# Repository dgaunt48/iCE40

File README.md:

# iCE40
Various iCE40 FPGA Projects.

## DaveFPGA
My custom iCE40 FPGA boards, see readme there for full description.

## iCE1k_VGA111
Display a 3bit VGA RGB test pattern on my iCE40hx1k based board.

## VIA_6522
6522 VIA iCE40 FPGA Core is now running on a real Vic20 and passing all tests on the diagnostic cartridge. It will boot to BASIC with the FPGA running the timers, performing the keyboard matrix scan and reading / writing serial data to the 1541.

## VIC_6560
Initial tests to recreate the VIC 6560 video IC.

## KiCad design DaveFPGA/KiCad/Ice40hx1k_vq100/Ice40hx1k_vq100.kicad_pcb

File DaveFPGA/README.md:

# Source
Skeleton rp2354 project to create a 25mhz clock and upload the FPGA bitstream.

# KiCAD\iCE40hx1k
My custom iCE40hx1k FPGA board with rp2354a I use when prototyping.

## Features
- Direct programming via SWD from the pico.
- Auto reset and much faster turn-around time than my other FT232H board.
- Cheaper BOM as both spi flash IC's are no longer needed.
- 3 Bit VGA from the pico for debugging.
- 2 User defined clock frequencies available from the pico.
- Upto 19 3v3 IO pins available to / from the pico.
- 40 5v <-> 3v3 bi-directional level shifters avaliable (some shared to the pico).
- 24 5v <-> 3v3 bi-directional open drain level shifters.
- Second 3 Bit VGA connector is availble from the FPGA.
- [link to ibom](KiCad/ibom_iCE40hx1k_vq100.html)

# KiCAD\iCE40hx4k
FT232H based iCE40hx4k board.  Not using this much anymore as i like
the workflow from the pico SWD.  Will probably make a new version of
this more like the 1k board when I need more IO pins or bitstream space.

## Features
- SPI flash programmed directly via FT232H.
- No direct control via the pico.
- Pico can be left running and reload the FPGA bitstream.
- [link to ibom](KiCad/ibom_iCE40hx4k_tq144.html)

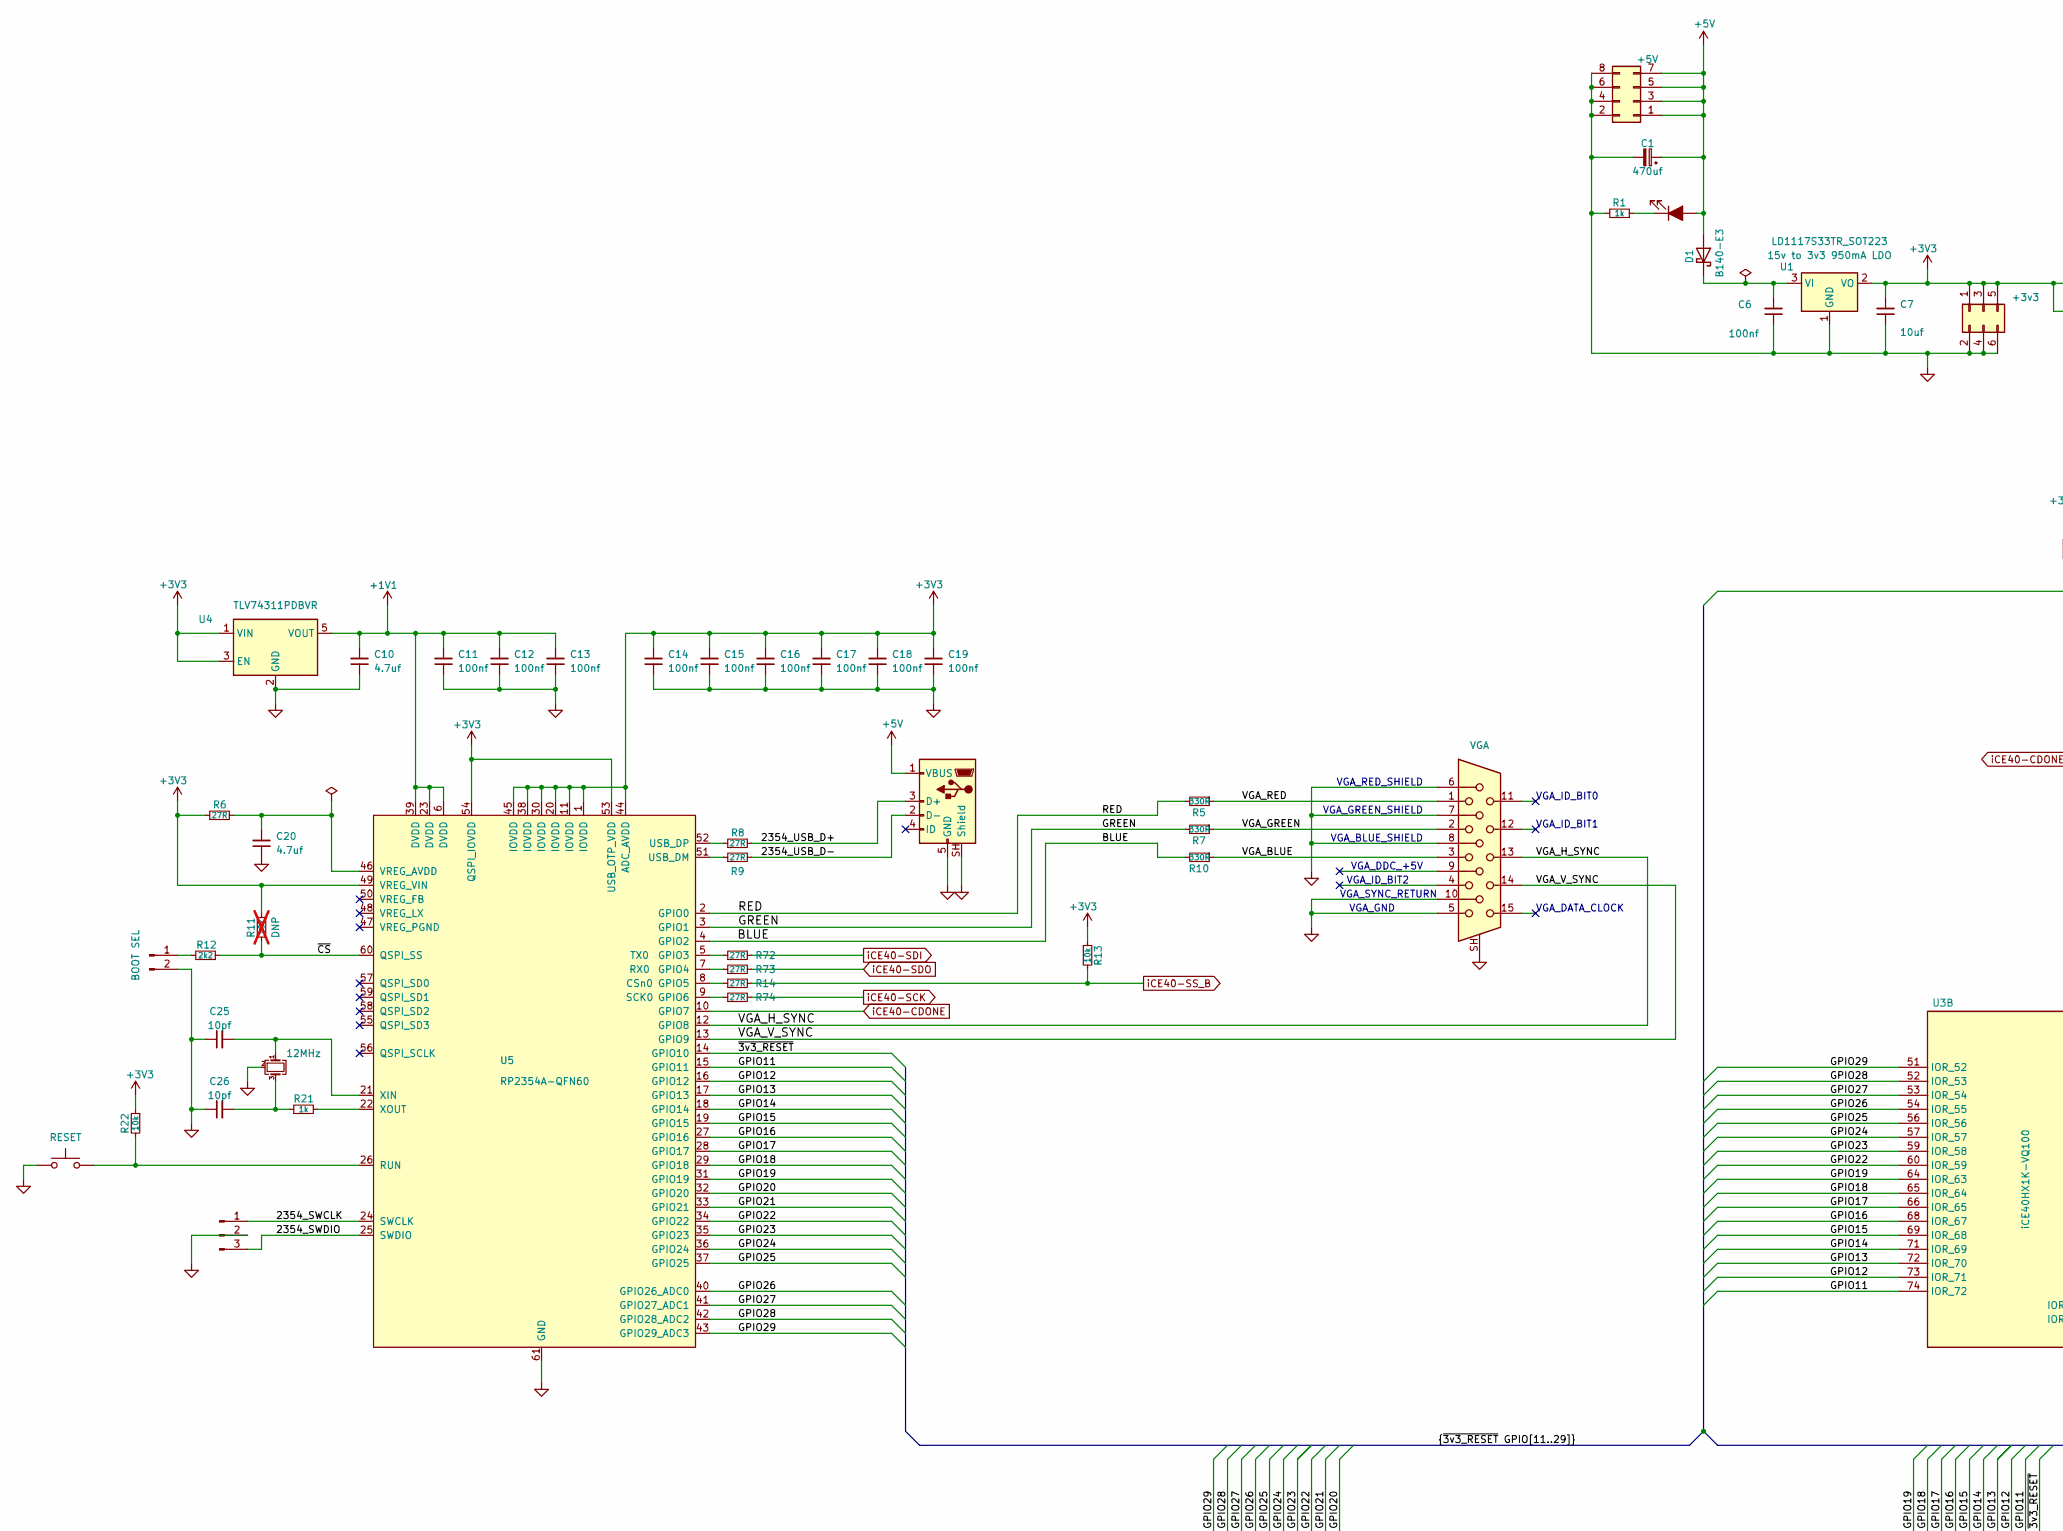
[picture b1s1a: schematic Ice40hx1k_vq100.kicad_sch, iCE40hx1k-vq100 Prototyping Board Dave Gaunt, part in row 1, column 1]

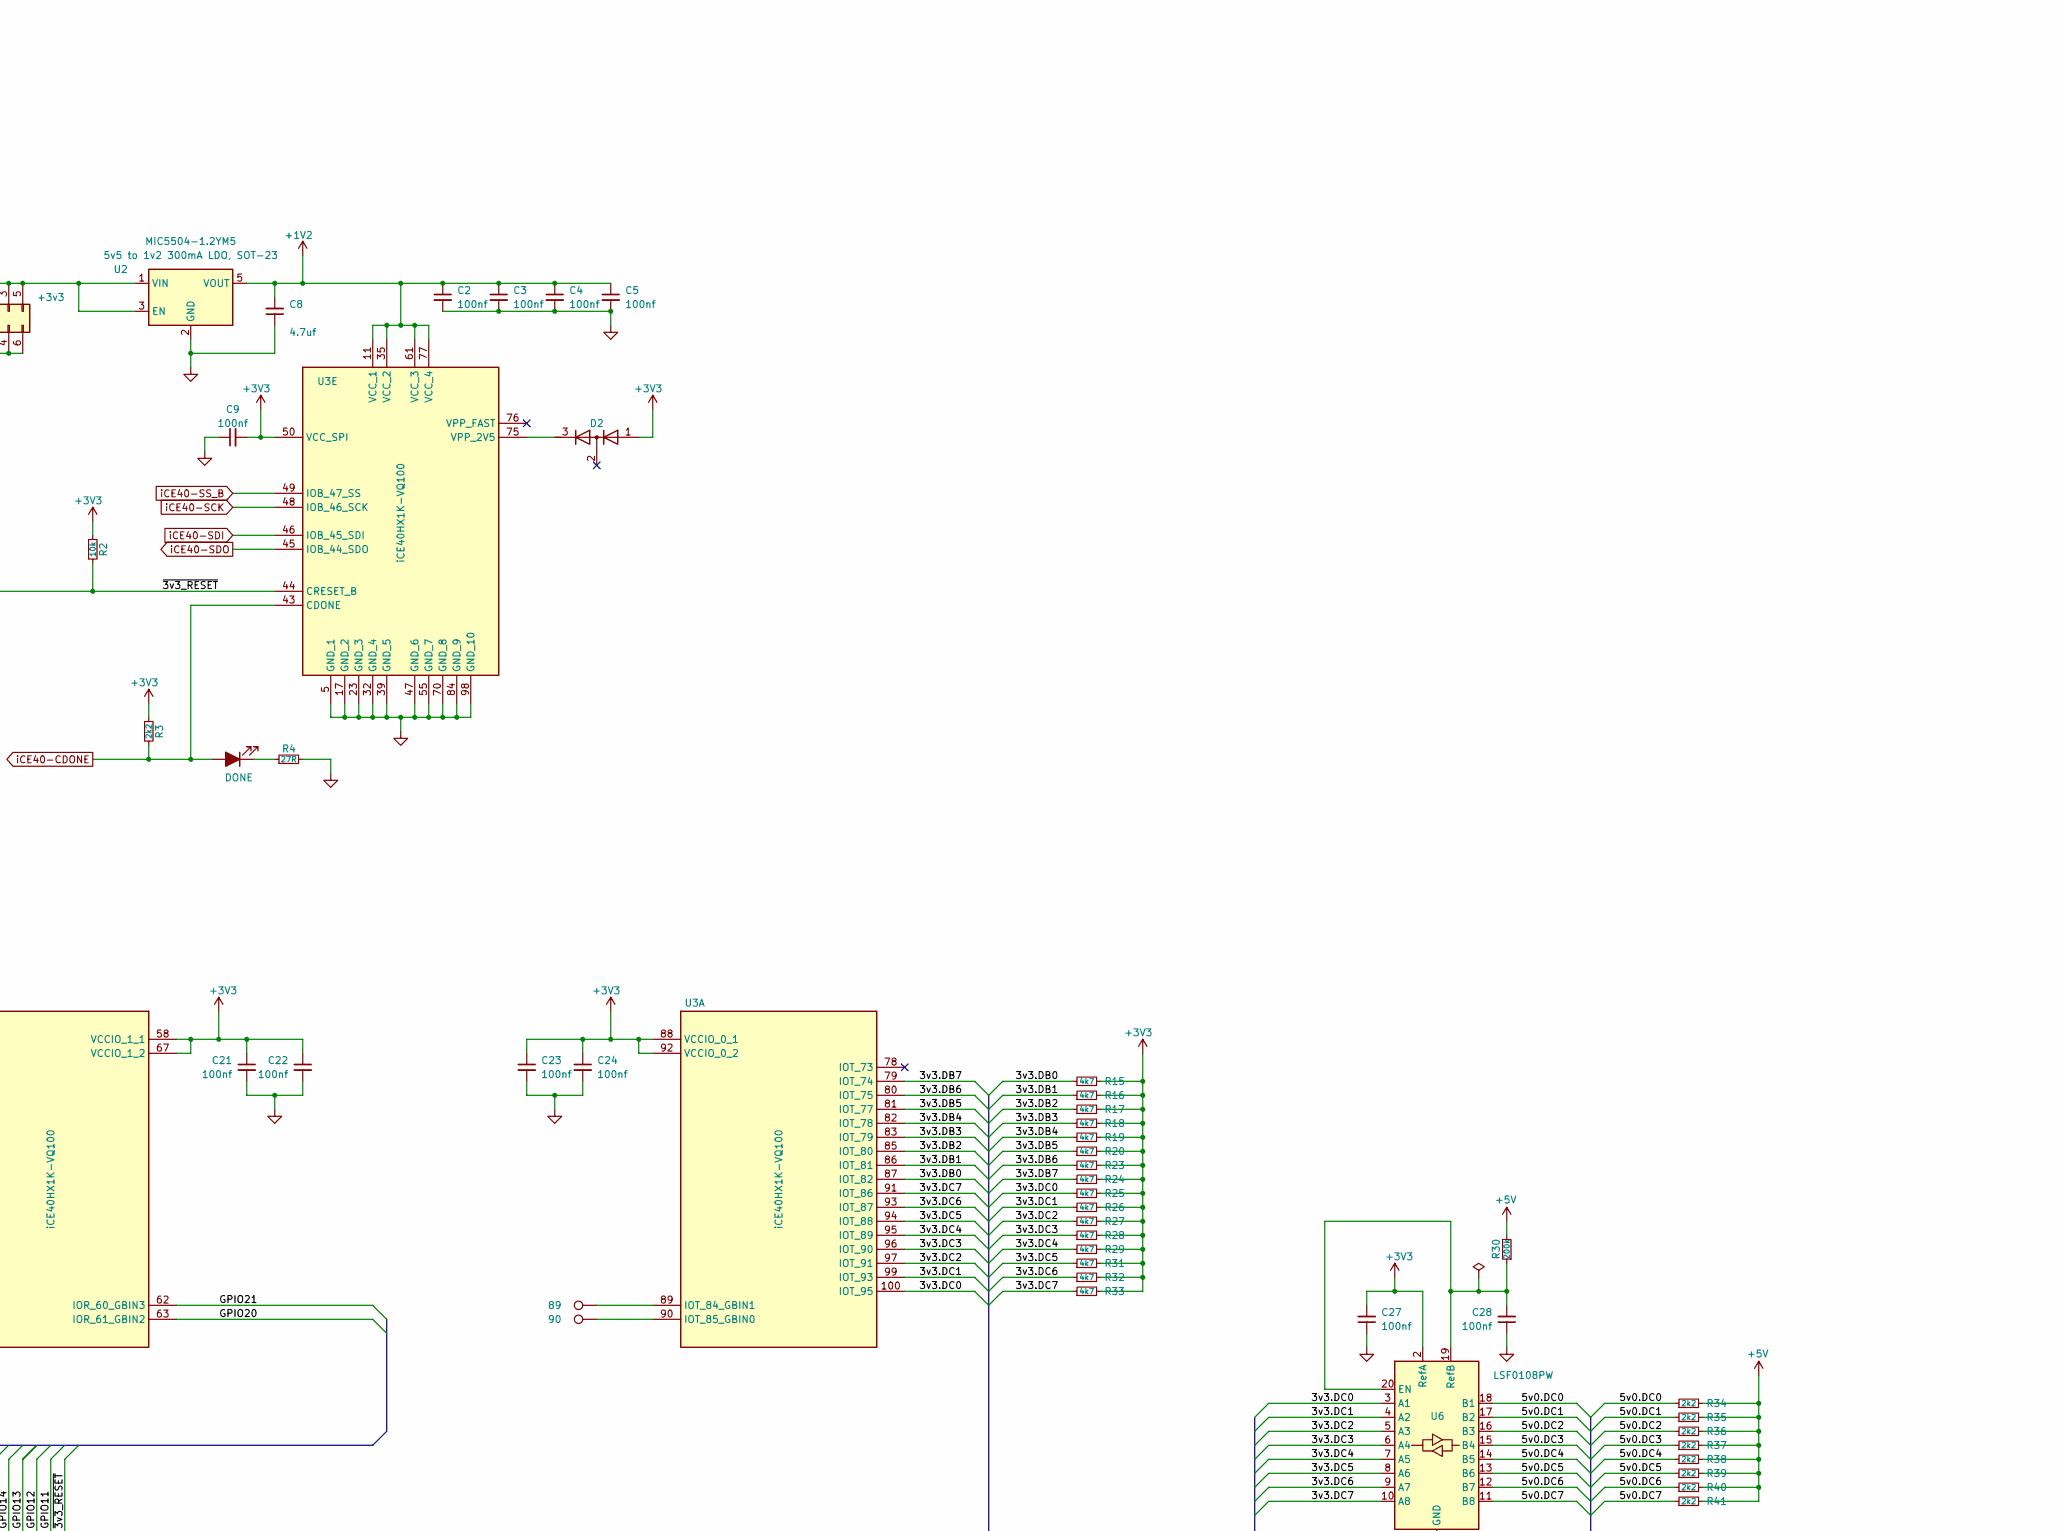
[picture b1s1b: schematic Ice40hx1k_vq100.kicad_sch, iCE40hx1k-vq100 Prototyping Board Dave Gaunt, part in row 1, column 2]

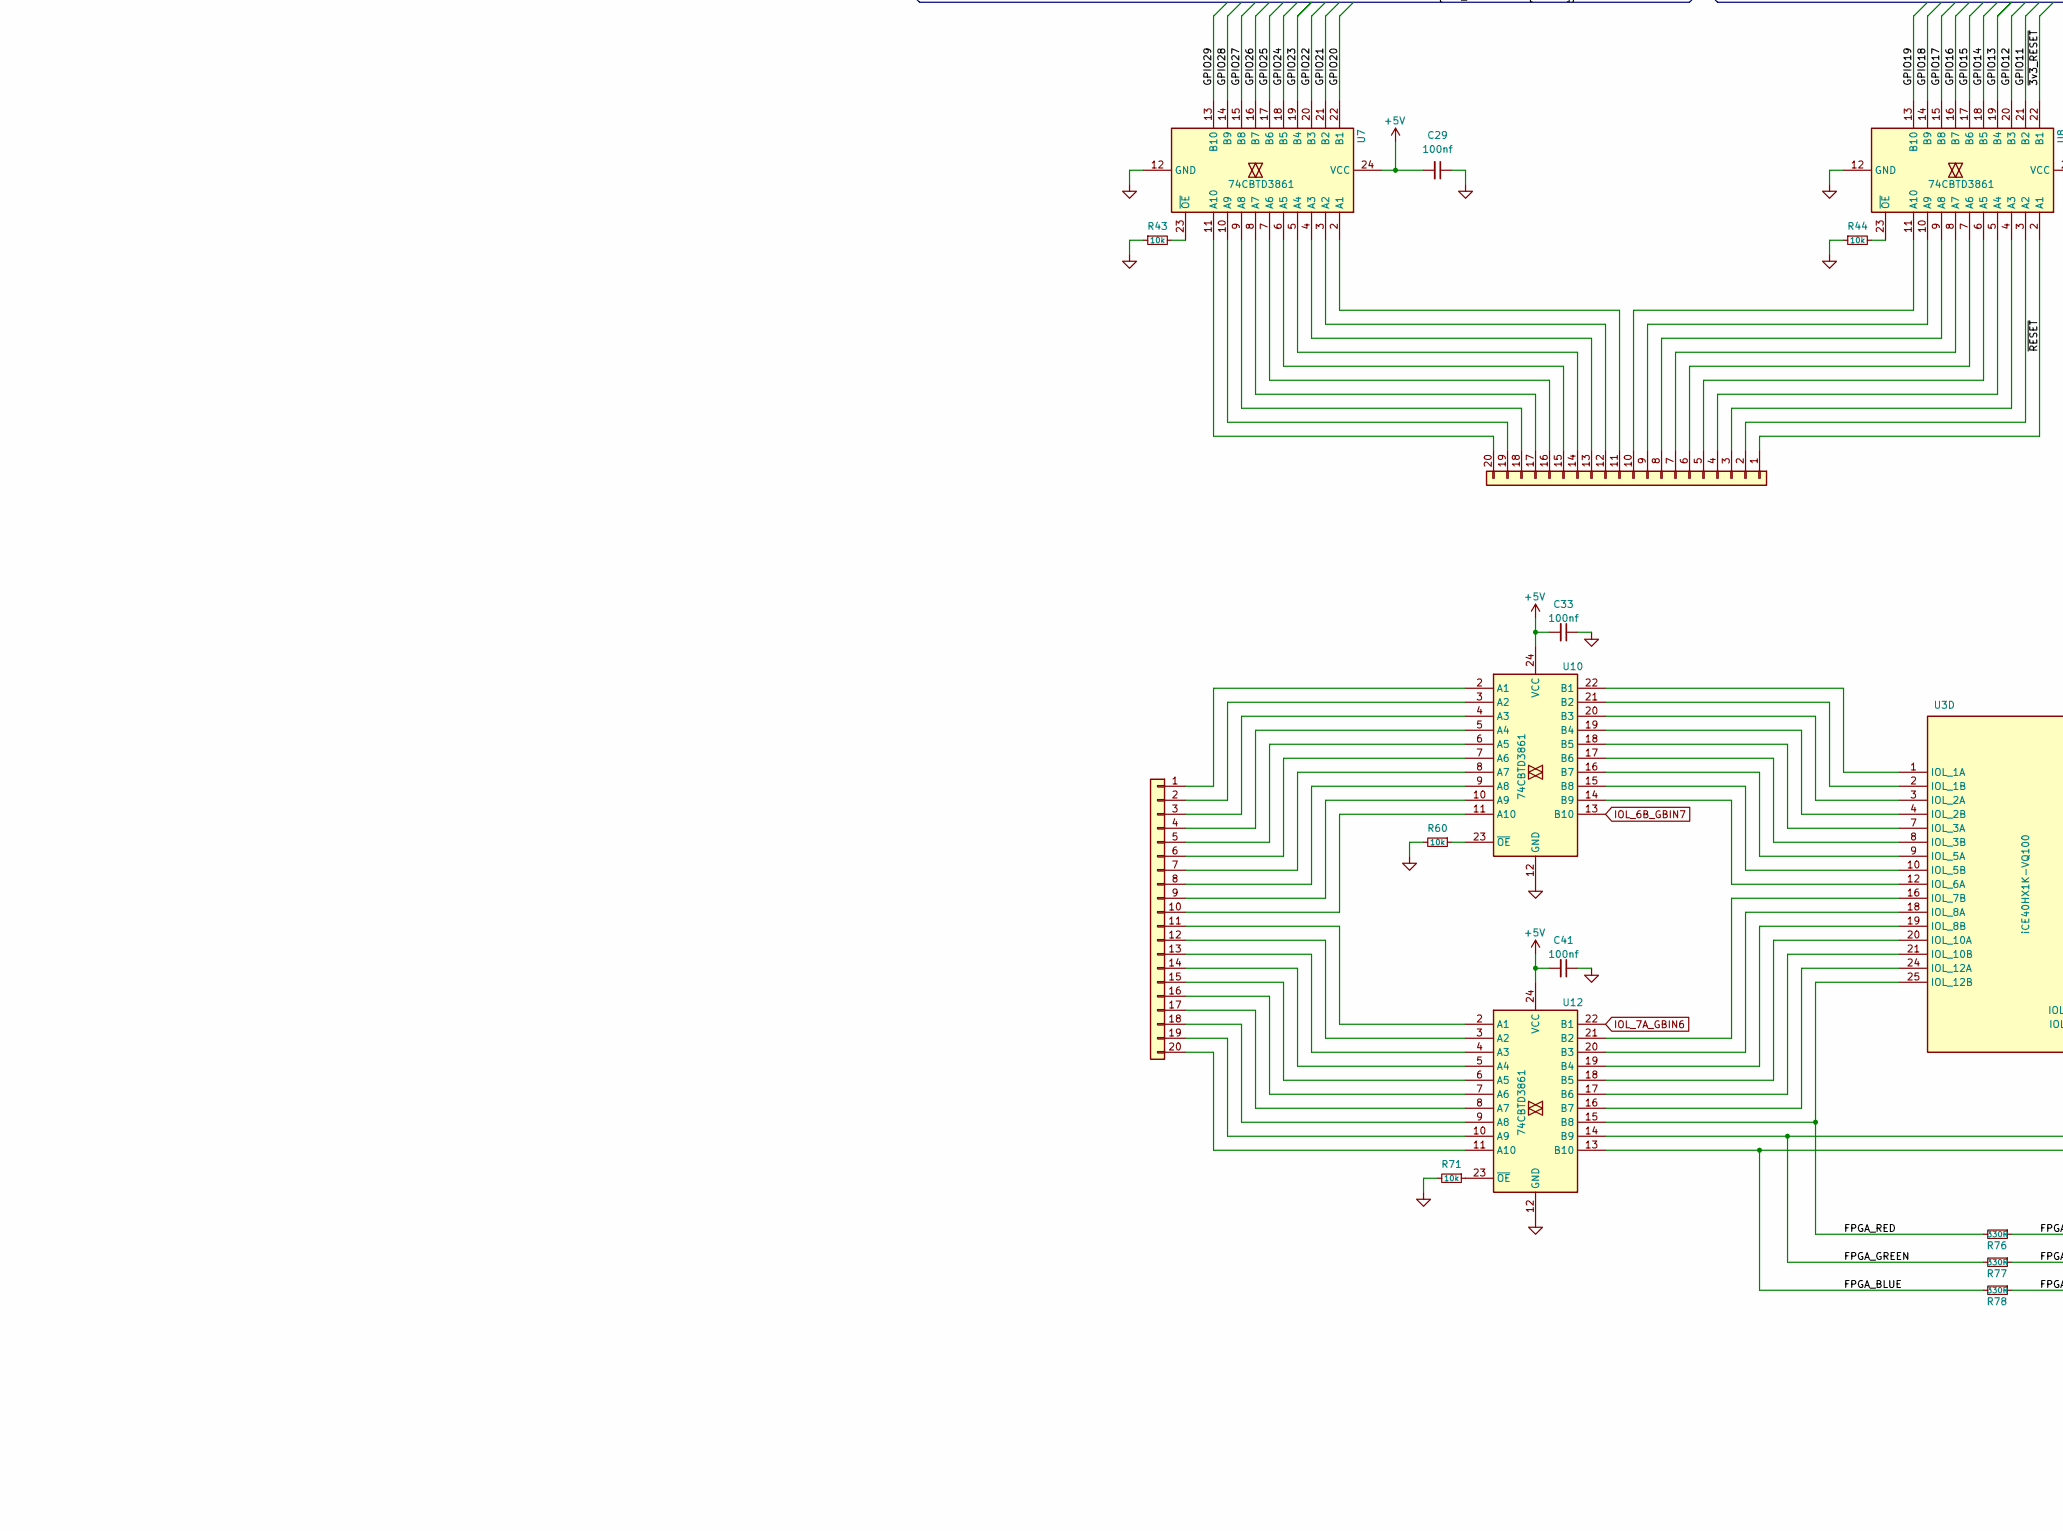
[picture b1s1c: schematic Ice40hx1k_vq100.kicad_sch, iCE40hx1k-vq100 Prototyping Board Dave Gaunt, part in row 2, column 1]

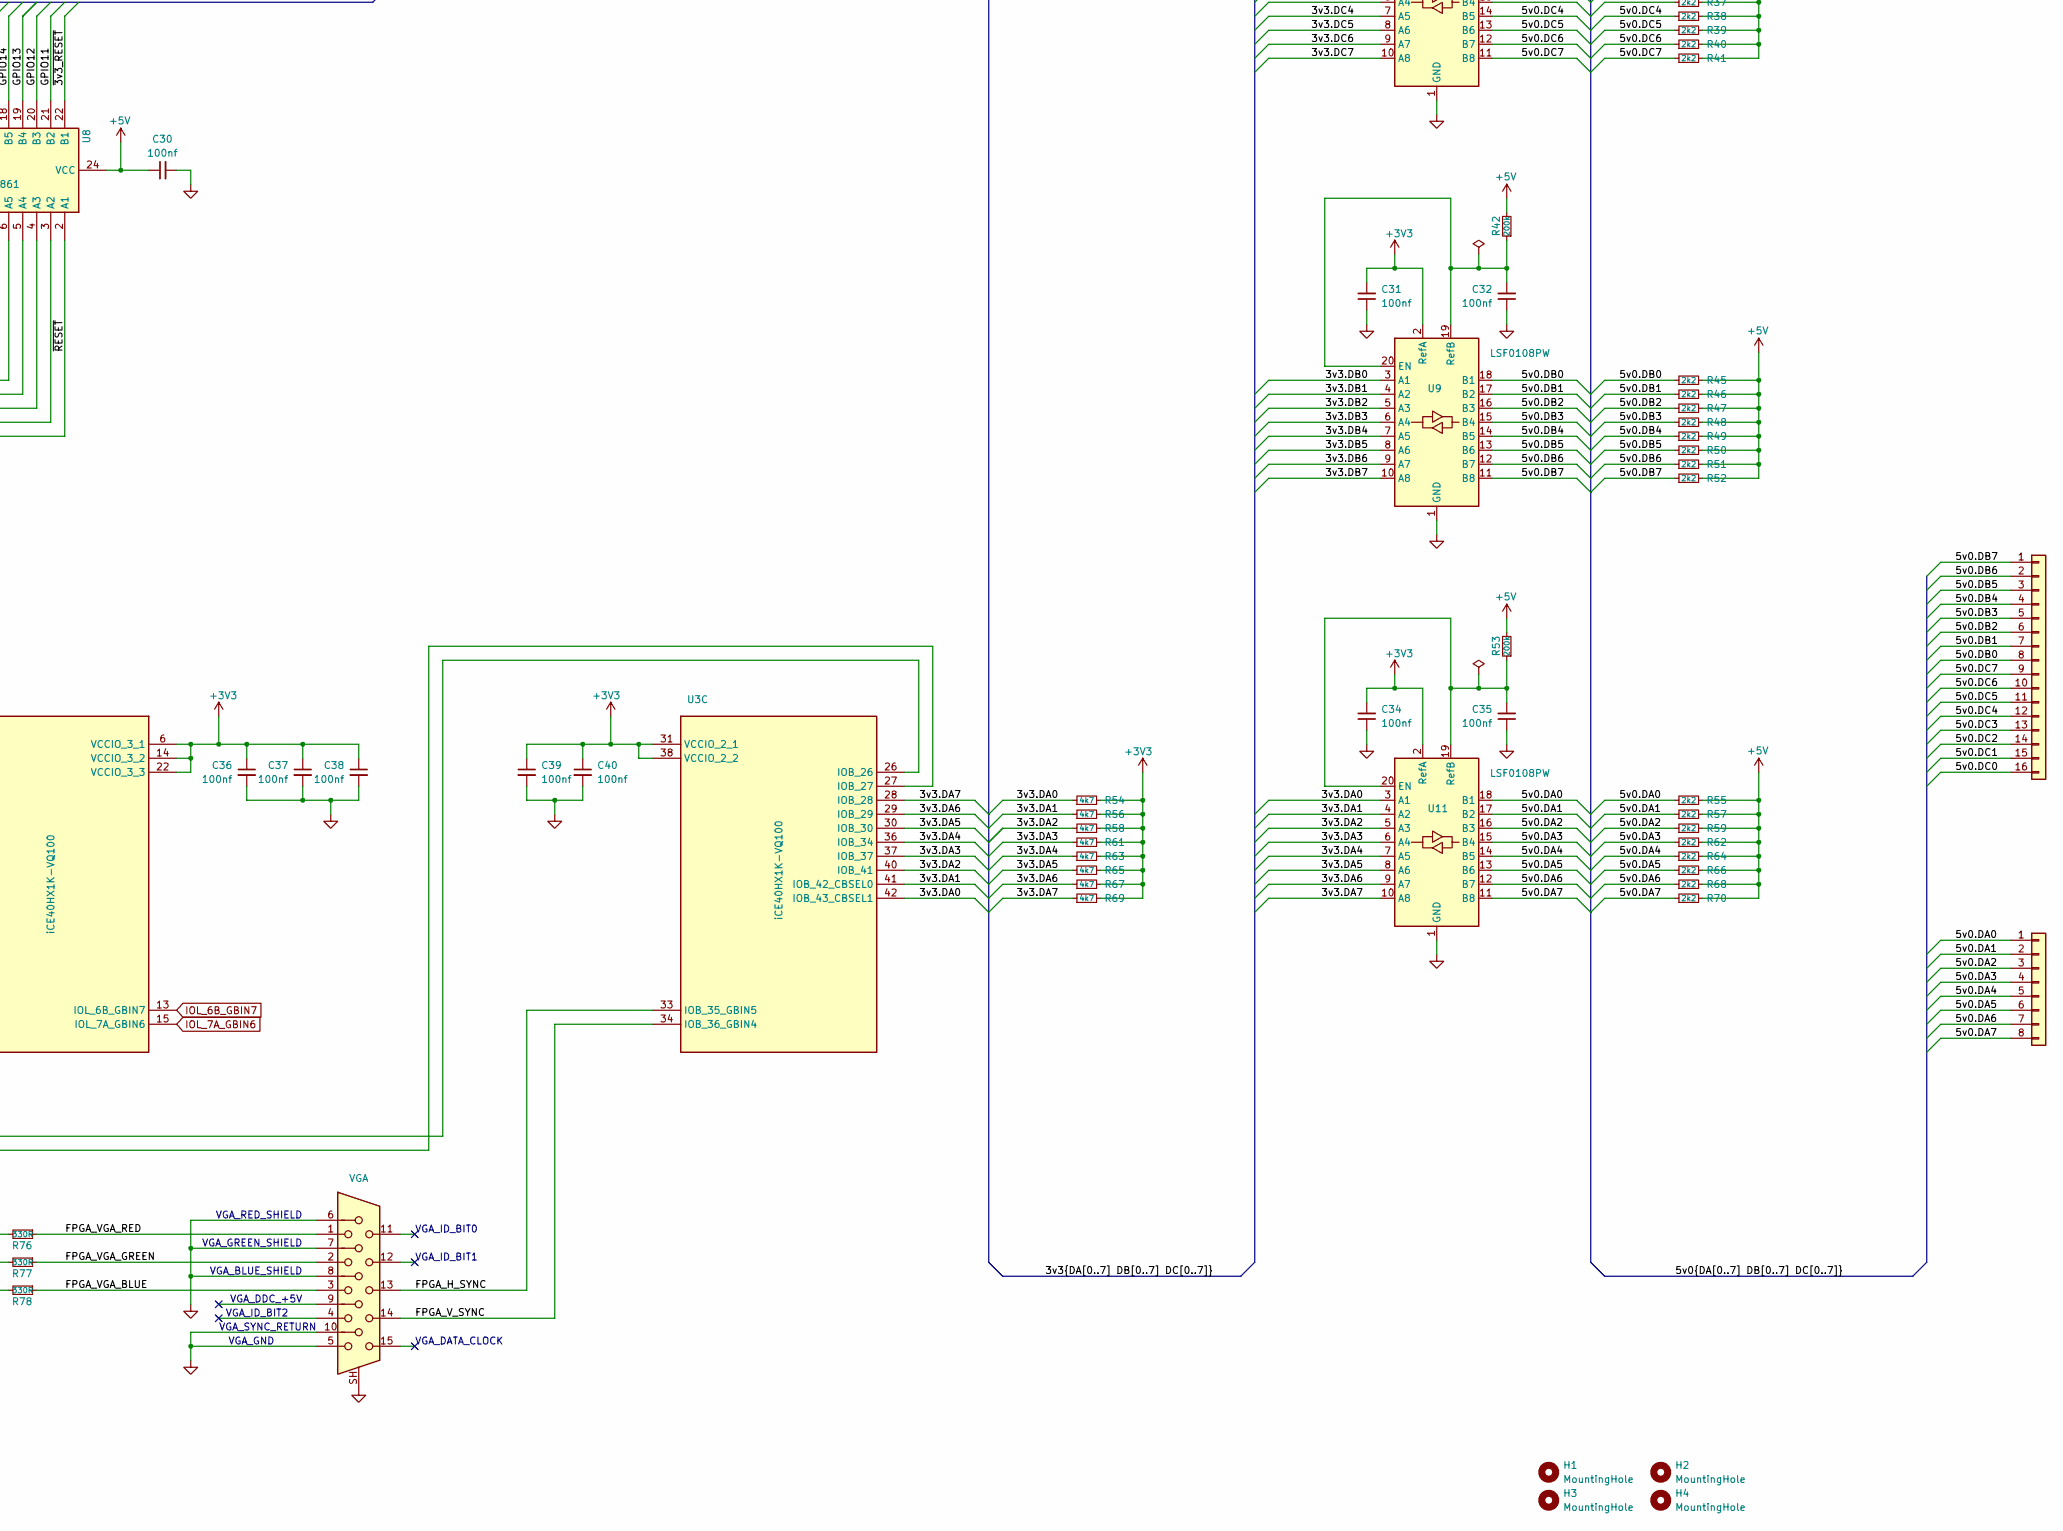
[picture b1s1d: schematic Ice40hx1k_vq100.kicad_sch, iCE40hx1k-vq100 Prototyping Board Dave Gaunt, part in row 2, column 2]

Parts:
C1: 470uf; CP_Radial_D5.0mm_P2.50mm
C2, C3, C4, C5, C6, C9, C11, C12, C13, C14, C15, C16, C17, C18, C19, C21, C22, C23, C24, C27, C28, C29, C30, C31, C32, C33, C34, C35, C36, C37, C38, C39, C40, C41: 100nf; C_0603_1608Metric
C7: 10uf; C_0805_2012Metric
C8, C10, C20: 4.7uf; C_0603_1608Metric
C25, C26: 10pf; C_0603_1608Metric
CDone1: DONE; LED_0805_2012Metric
D1: B140-E3; D_SOD-123
D2: D_Dual_Series_ACK; SOT-23
H1, H2, H3, H4: MountingHole; MountingHole_3.5mm
J1: +5V; PinHeader_2x04_P2.54mm_Vertical
J2: +3v3; PinHeader_2x03_P2.54mm_Vertical
J3: USB_B_Micro; USB_Micro-B_Amphenol_10103594-0001LF_Horizontal
J4, J10: VGA; DSUB-15
J5: SWD; PinHeader_1x03_P2.54mm_Vertical
J6, J8: PinHeader_1x20_P2.54mm_Vertical
J7: PinHeader_1x16_P2.54mm_Vertical
J9: PinHeader_1x08_P2.54mm_Vertical
Je1: BOOT SEL; PinHeader_1x02_P2.54mm_Vertical
Power1: POWER; LED_0805_2012Metric
R1, R21: 1k; R_0603_1608Metric
R2, R13, R22, R43, R44, R60, R71: 10k; R_0603_1608Metric
R3, R12, R34, R35, R36, R37, R38, R39, R40, R41, R45, R46, R47, R48, R49, R50, R51, R52, R55, R57, R59, R62, R64, R66, R68, R70: 2k2; R_0603_1608Metric
R4, R6, R8, R9, R14, R72, R73, R74: 27R; R_0603_1608Metric
R5, R7, R10, R76, R77, R78: 330R; R_0603_1608Metric
R11: 10k; R_0603_1608Metric; not fitted
R15, R16, R17, R18, R19, R20, R23, R24, R25, R26, R27, R28, R29, R31, R32, R33, R54, R56, R58, R61, R63, R65, R67, R69: 4k7; R_0603_1608Metric
R30, R42, R53: 200k; R_0603_1608Metric
S1: RESET; SW_PUSH_6mm_H4.3mm; Mouser Part Number 653-B3F-1052-G
TP1: 89; TestPoint_Pad_D1.0mm
TP2: 90; TestPoint_Pad_D1.0mm
U1: LD1117S33TR_SOT223; SOT-223-3_TabPin2; Voltage 3v3
U2: MIC5504-1.2YM5; SOT-23-5; Voltage 1v2
U3: iCE40HX1K-VQ100; LQFP-100_14x14mm_P0.5mm; Mouser Part Number 842-ICE40HX4K-TQ144
U4: TLV74311PDBVR; SOT-23-5; Voltage 1v1
U5: RP2354A-QFN60; RP2350A_QFN-60_EP_7.75x7.75_Pitch0.4mm
U6, U9, U11: LSF0108PW; TSSOP-20_4.4x6.5mm_P0.65mm
U7, U8, U10, U12: 74CBTD3861; SSOP-24_3.9x8.7mm_P0.635mm
Y1: 12MHz; Crystal_SMD_SeikoEpson_FA238V-4Pin_3.2x2.5mm

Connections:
+1V1: C10.2, C11.2, C12.2, C13.2, U4.5 (VOUT), U5.6 (DVDD), U5.23 (DVDD), U5.39 (DVDD)
+1V2: C2.1, C3.1, C4.1, C5.1, C8.2, U2.5 (VOUT), U3.11 (VCC_1), U3.35 (VCC_2), U3.61 (VCC_3), U3.77 (VCC_4)
+3V3: C7.2, C9.2, C14.2, C15.2, C16.2, C17.2, C18.2, C19.2, C21.1, C22.1, C23.1, C24.1, C27.2, C31.2, C34.2, C36.1, C37.1, C38.1, C39.1, C40.1, D2.1 (A), J2.1, J2.3, J2.5, R2.1, R3.1, R6.1, R11.1, R13.1, R15.2, R16.2, R17.2, R18.2, R19.2, R20.2, R22.1, R23.2, R24.2, R25.2, R26.2, R27.2, R28.2, R29.2, R31.2, R32.2, R33.2, R54.2, R56.2, R58.2, R61.2, R63.2, R65.2, R67.2, R69.2, U1.2 (VO), U2.1 (VIN), U2.3 (EN), U3.6 (VCCIO_3_1), U3.14 (VCCIO_3_2), U3.22 (VCCIO_3_3), U3.31 (VCCIO_2_1), U3.38 (VCCIO_2_2), U3.50 (VCC_SPI), U3.58 (VCCIO_1_1), U3.67 (VCCIO_1_2), U3.88 (VCCIO_0_1), U3.92 (VCCIO_0_2), U4.1 (VIN), U4.3 (EN), U5.1 (IOVDD), U5.11 (IOVDD), U5.20 (IOVDD), U5.30 (IOVDD), U5.38 (IOVDD), U5.44 (ADC_AVDD), U5.45 (IOVDD), U5.49 (VREG_VIN), U5.53 (USB_OTP_VDD), U5.54 (QSPI_IOVDD), U6.2 (RefA), U9.2 (RefA), U11.2 (RefA); also elsewhere on the board
+5V: C1.1, C29.2, C30.1, C33.2, C41.2, D1.2 (A), J1.1, J1.3, J1.5, J1.7, J3.1 (VBUS), Power1.2 (A), R30.2, R34.2, R35.2, R36.2, R37.2, R38.2, R39.2, R40.2, R41.2, R42.2, R45.2, R46.2, R47.2, R48.2, R49.2, R50.2, R51.2, R52.2, R53.2, R55.2, R57.2, R59.2, R62.2, R64.2, R66.2, R68.2, R70.2, U7.24 (VCC), U8.24 (VCC), U10.24 (VCC), U12.24 (VCC)
/3v3.DA0: R54.1, U3.42 (IOB_43_CBSEL1), U11.3 (A1)
/3v3.DA1: R56.1, U3.41 (IOB_42_CBSEL0), U11.4 (A2)
/3v3.DA2: R58.1, U3.40 (IOB_41), U11.5 (A3)
/3v3.DA3: R61.1, U3.37 (IOB_37), U11.6 (A4)
/3v3.DA4: R63.1, U3.36 (IOB_34), U11.7 (A5)
/3v3.DA5: R65.1, U3.30 (IOB_30), U11.8 (A6)
/3v3.DA6: R67.1, U3.29 (IOB_29), U11.9 (A7)
/3v3.DA7: R69.1, U3.28 (IOB_28), U11.10 (A8)
/3v3.DB0: R15.1, U3.87 (IOT_82), U9.3 (A1)
/3v3.DB1: R16.1, U3.86 (IOT_81), U9.4 (A2)
/3v3.DB2: R17.1, U3.85 (IOT_80), U9.5 (A3)
/3v3.DB3: R18.1, U3.83 (IOT_79), U9.6 (A4)
/3v3.DB4: R19.1, U3.82 (IOT_78), U9.7 (A5)
/3v3.DB5: R20.1, U3.81 (IOT_77), U9.8 (A6)
/3v3.DB6: R23.1, U3.80 (IOT_75), U9.9 (A7)
/3v3.DB7: R24.1, U3.79 (IOT_74), U9.10 (A8)
/3v3.DC0: R25.1, U3.100 (IOT_95), U6.3 (A1)
/3v3.DC1: R26.1, U3.99 (IOT_93), U6.4 (A2)
/3v3.DC2: R27.1, U3.97 (IOT_91), U6.5 (A3)
/3v3.DC3: R28.1, U3.96 (IOT_90), U6.6 (A4)
/3v3.DC4: R29.1, U3.95 (IOT_89), U6.7 (A5)
/3v3.DC5: R31.1, U3.94 (IOT_88), U6.8 (A6)
/3v3.DC6: R32.1, U3.93 (IOT_87), U6.9 (A7)
/3v3.DC7: R33.1, U3.91 (IOT_86), U6.10 (A8)
/5v0.DA0: J9.1, R55.1, U11.18 (B1)
/5v0.DA1: J9.2, R57.1, U11.17 (B2)
/5v0.DA2: J9.3, R59.1, U11.16 (B3)
/5v0.DA3: J9.4, R62.1, U11.15 (B4)
/5v0.DA4: J9.5, R64.1, U11.14 (B5)
/5v0.DA5: J9.6, R66.1, U11.13 (B6)
/5v0.DA6: J9.7, R68.1, U11.12 (B7)
/5v0.DA7: J9.8, R70.1, U11.11 (B8)
/5v0.DB0: J7.8, R45.1, U9.18 (B1)
/5v0.DB1: J7.7, R46.1, U9.17 (B2)
/5v0.DB2: J7.6, R47.1, U9.16 (B3)
/5v0.DB3: J7.5, R48.1, U9.15 (B4)
/5v0.DB4: J7.4, R49.1, U9.14 (B5)
/5v0.DB5: J7.3, R50.1, U9.13 (B6)
/5v0.DB6: J7.2, R51.1, U9.12 (B7)
/5v0.DB7: J7.1, R52.1, U9.11 (B8)
/5v0.DC0: J7.16, R34.1, U6.18 (B1)
/5v0.DC1: J7.15, R35.1, U6.17 (B2)
/5v0.DC2: J7.14, R36.1, U6.16 (B3)
/5v0.DC3: J7.13, R37.1, U6.15 (B4)
/5v0.DC4: J7.12, R38.1, U6.14 (B5)
/5v0.DC5: J7.11, R39.1, U6.13 (B6)
/5v0.DC6: J7.10, R40.1, U6.12 (B7)
/5v0.DC7: J7.9, R41.1, U6.11 (B8)
/2354_SWCLK: J5.1, U5.24 (SWCLK)
/2354_SWDIO: J5.3, U5.25 (SWDIO)
/2354_USB_D+: J3.3 (D+), R8.2
/2354_USB_D-: J3.2 (D-), R9.2
/BLUE: R10.2, U5.4 (GPIO2)
/FPGA_BLUE: R78.2, U3.27 (IOB_27), U12.13 (B10)
/FPGA_GREEN: R77.2, U3.26 (IOB_26), U12.14 (B9)
/FPGA_H_SYNC: J10.13, U3.33 (IOB_35_GBIN5)
/FPGA_RED: R76.2, U3.25 (IOL_12B), U12.15 (B8)
/FPGA_VGA_BLUE: J10.3, R78.1
/FPGA_VGA_GREEN: J10.2, R77.1
/FPGA_VGA_RED: J10.1, R76.1
/FPGA_V_SYNC: J10.14, U3.34 (IOB_36_GBIN4)
/GPIO11: U3.74 (IOR_72), U5.15 (GPIO11), U8.21 (B2)
/GPIO12: U3.73 (IOR_71), U5.16 (GPIO12), U8.20 (B3)
/GPIO13: U3.72 (IOR_70), U5.17 (GPIO13), U8.19 (B4)
/GPIO14: U3.71 (IOR_69), U5.18 (GPIO14), U8.18 (B5)
/GPIO15: U3.69 (IOR_68), U5.19 (GPIO15), U8.17 (B6)
/GPIO16: U3.68 (IOR_67), U5.27 (GPIO16), U8.16 (B7)
/GPIO17: U3.66 (IOR_65), U5.28 (GPIO17), U8.15 (B8)
/GPIO18: U3.65 (IOR_64), U5.29 (GPIO18), U8.14 (B9)
/GPIO19: U3.64 (IOR_63), U5.31 (GPIO19), U8.13 (B10)
/GPIO20: U3.63 (IOR_61_GBIN2), U5.32 (GPIO20), U7.22 (B1)
/GPIO21: U3.62 (IOR_60_GBIN3), U5.33 (GPIO21), U7.21 (B2)
/GPIO22: U3.60 (IOR_59), U5.34 (GPIO22), U7.20 (B3)
/GPIO23: U3.59 (IOR_58), U5.35 (GPIO23), U7.19 (B4)
/GPIO24: U3.57 (IOR_57), U5.36 (GPIO24), U7.18 (B5)
/GPIO25: U3.56 (IOR_56), U5.37 (GPIO25), U7.17 (B6)
/GPIO26: U3.54 (IOR_55), U5.40 (GPIO26_ADC0), U7.16 (B7)
/GPIO27: U3.53 (IOR_54), U5.41 (GPIO27_ADC1), U7.15 (B8)
/GPIO28: U3.52 (IOR_53), U5.42 (GPIO28_ADC2), U7.14 (B9)
/GPIO29: U3.51 (IOR_52), U5.43 (GPIO29_ADC3), U7.13 (B10)
/GREEN: R7.2, U5.3 (GPIO1)
/RED: R5.2, U5.2 (GPIO0)
/VGA_BLUE: J4.3, R10.1
/VGA_GREEN: J4.2, R7.1
/VGA_H_SYNC: J4.13, U5.12 (GPIO8)
/VGA_RED: J4.1, R5.1
/VGA_V_SYNC: J4.14, U5.13 (GPIO9)
/~3v3_RESET: R2.2, U3.44 (CRESET_B), U5.14 (GPIO10), U8.22 (B1)
/~CS: R11.2, R12.1, U5.60 (QSPI_SS)
/~RESET: J6.1, U8.2 (A1)
GND: C1.2, C2.2, C3.2, C4.2, C5.2, C6.1, C7.1, C8.1, C9.1, C10.1, C11.1, C12.1, C13.1, C14.1, C15.1, C16.1, C17.1, C18.1, C19.1, C20.1, C21.2, C22.2, C23.2, C24.2, C25.1, C26.1, C27.1, C28.1, C29.1, C30.2, C31.1, C32.1, C33.1, C34.1, C35.1, C36.2, C37.2, C38.2, C39.2, C40.2, C41.1, J1.2, J1.4, J1.6, J1.8, J2.2, J2.4, J2.6, J3.5 (GND), J3.SH (Shield), J4.5, J4.6, J4.7, J4.8, J4.10, J4.SH, J5.2, J10.5, J10.6, J10.7, J10.8, J10.10, J10.SH, Je1.2, R1.2, R4.2, R43.1, R44.1, R60.2, R71.2, S1.2, U1.1 (GND), U2.2 (GND), U3.5 (GND_1), U3.17 (GND_2), U3.23 (GND_3), U3.32 (GND_4), U3.39 (GND_5), U3.47 (GND_6), U3.55 (GND_7), U3.70 (GND_8), U3.84 (GND_9), U3.98 (GND_10), U4.2 (GND), U5.61 (GND), U6.1 (GND), U7.12 (GND), U8.12 (GND), U9.1 (GND), U10.12 (GND), U11.1 (GND), U12.12 (GND), Y1.2 (G), Y1.4 (G); also elsewhere on the board
IOL_6B_GBIN7: U3.13 (IOL_6B_GBIN7), U10.13 (B10)
IOL_7A_GBIN6: U3.15 (IOL_7A_GBIN6), U12.22 (B1)
unnamed: C26.2, R21.1, Y1.3
unnamed: CDone1.1 (K), R4.1
unnamed: C6.2, D1.1 (K), U1.3 (VI)
unnamed: D2.3 (K), U3.75 (VPP_2V5)
unnamed: J6.2, U8.3 (A2)
unnamed: J6.3, U8.4 (A3)
unnamed: J6.4, U8.5 (A4)
unnamed: J6.5, U8.6 (A5)
unnamed: J6.6, U8.7 (A6)
unnamed: J6.7, U8.8 (A7)
unnamed: J6.8, U8.9 (A8)
unnamed: J6.9, U8.10 (A9)
unnamed: J6.10, U8.11 (A10)
unnamed: J6.11, U7.2 (A1)
unnamed: J6.12, U7.3 (A2)
unnamed: J6.13, U7.4 (A3)
unnamed: J6.14, U7.5 (A4)
unnamed: J6.15, U7.6 (A5)
unnamed: J6.16, U7.7 (A6)
unnamed: J6.17, U7.8 (A7)
unnamed: J6.18, U7.9 (A8)
unnamed: J6.19, U7.10 (A9)
unnamed: J6.20, U7.11 (A10)
unnamed: J8.1, U10.2 (A1)
unnamed: J8.2, U10.3 (A2)
unnamed: J8.3, U10.4 (A3)
unnamed: J8.4, U10.5 (A4)
unnamed: J8.5, U10.6 (A5)
unnamed: J8.6, U10.7 (A6)
unnamed: J8.7, U10.8 (A7)
unnamed: J8.8, U10.9 (A8)
unnamed: J8.9, U10.10 (A9)
unnamed: J8.10, U10.11 (A10)
unnamed: J8.11, U12.2 (A1)
unnamed: J8.12, U12.3 (A2)
unnamed: J8.13, U12.4 (A3)
unnamed: J8.14, U12.5 (A4)
unnamed: J8.15, U12.6 (A5)
unnamed: J8.16, U12.7 (A6)
unnamed: J8.17, U12.8 (A7)
unnamed: J8.18, U12.9 (A8)
unnamed: J8.19, U12.10 (A9)
unnamed: J8.20, U12.11 (A10)
unnamed: Je1.1, R12.2
unnamed: Power1.1 (K), R1.1
unnamed: TP1.1 (1_1), U3.89 (IOT_84_GBIN1)
unnamed: TP2.1 (1_1), U3.90 (IOT_85_GBIN0)
unnamed: R72.1, U5.5 (GPIO3)
unnamed: R73.1, U5.7 (GPIO4)
unnamed: R14.1, U5.8 (GPIO5)
unnamed: R74.1, U5.9 (GPIO6)
unnamed: R22.2, S1.1, U5.26 (RUN)
unnamed: R9.1, U5.51 (USB_DM)
unnamed: R8.1, U5.52 (USB_DP)
unnamed: C20.2, R6.2, U5.46 (VREG_AVDD)
unnamed: C25.2, U5.21 (XIN), Y1.1
unnamed: R21.2, U5.22 (XOUT)
unnamed: C28.2, R30.1, U6.19 (RefB), U6.20 (EN)
unnamed: R43.2, U7.23 (~OE)
unnamed: R44.2, U8.23 (~OE)
unnamed: C32.2, R42.1, U9.19 (RefB), U9.20 (EN)
unnamed: U3.1 (IOL_1A), U10.22 (B1)
unnamed: U3.2 (IOL_1B), U10.21 (B2)
unnamed: U3.3 (IOL_2A), U10.20 (B3)
unnamed: U3.4 (IOL_2B), U10.19 (B4)
unnamed: U3.7 (IOL_3A), U10.18 (B5)
unnamed: U3.8 (IOL_3B), U10.17 (B6)
unnamed: U3.9 (IOL_5A), U10.16 (B7)
unnamed: U3.10 (IOL_5B), U10.15 (B8)
unnamed: U3.12 (IOL_6A), U10.14 (B9)
unnamed: R60.1, U10.23 (~OE)
unnamed: C35.2, R53.1, U11.19 (RefB), U11.20 (EN)
unnamed: U3.16 (IOL_7B), U12.21 (B2)
unnamed: U3.18 (IOL_8A), U12.20 (B3)
unnamed: U3.19 (IOL_8B), U12.19 (B4)
unnamed: U3.20 (IOL_10A), U12.18 (B5)
unnamed: U3.21 (IOL_10B), U12.17 (B6)
unnamed: U3.24 (IOL_12A), U12.16 (B7)
unnamed: R71.1, U12.23 (~OE)
iCE40-CDONE: CDone1.2 (A), R3.2, U3.43 (CDONE), U5.10 (GPIO7)
iCE40-SCK: R74.2, U3.48 (IOB_46_SCK)
iCE40-SDI: R72.2, U3.46 (IOB_45_SDI)
iCE40-SDO: R73.2, U3.45 (IOB_44_SDO)
iCE40-SS_B: R13.2, R14.2, U3.49 (IOB_47_SS)

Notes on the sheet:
VGA_GREEN_SHIELD
VGA_GND
VGA_DDC_+5V
VGA_SYNC_RETURN
VGA_DATA_CLOCK
VGA_BLUE_SHIELD
VGA_ID_BIT1
VGA_ID_BIT0
VGA_RED_SHIELD
VGA_ID_BIT2
